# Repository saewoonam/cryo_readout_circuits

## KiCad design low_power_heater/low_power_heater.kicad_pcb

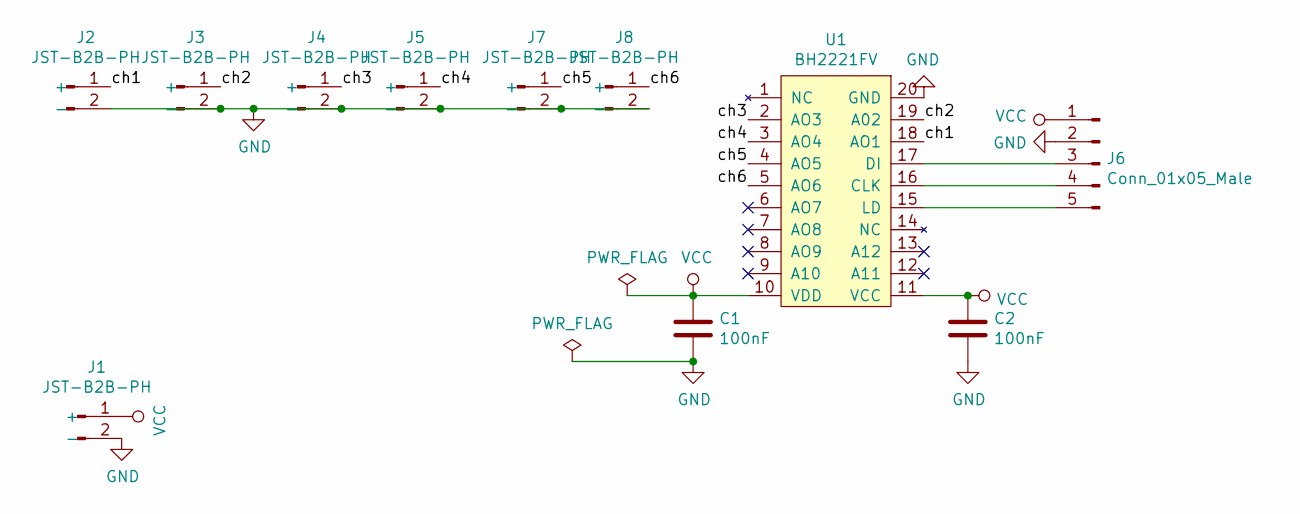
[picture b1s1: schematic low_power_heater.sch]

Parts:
C1, C2: 100nF; C_0603_1608Metric_Pad1.05x0.95mm_HandSolder; MPN CC0603KRX7R9BB104; LCSC C14663
J1, J2, J3, J4, J5, J7, J8: JST-B2B-PH; JST_PH_S2B-PH-SM4-TB_1x02-1MP_P2.00mm_Horizontal; MPN S2B-PH-SM4-TB(LF)(SN); LCSC C295747
J6: Conn_01x05_Male; PinHeader_1x05_P2.54mm_Horizontal; MPN PZ254R-11-05P; LCSC C492413
U1: BH2221FV; SSOP-20_4.4x6.5mm_P0.65mm; MPN BH2221FV-E2; LCSC C2679449

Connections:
/ch1: J2.1 (+), U1.18 (AO1)
/ch2: J3.1 (+), U1.19 (A02)
/ch3: J4.1 (+), U1.2 (AO3)
/ch4: J5.1 (+), U1.3 (AO4)
/ch5: J7.1 (+), U1.4 (AO5)
/ch6: J8.1 (+), U1.5 (AO6)
GND: C1.2, C2.2, J1.2 (-), J2.2 (-), J3.2 (-), J4.2 (-), J5.2 (-), J6.2, J7.2 (-), J8.2 (-), U1.20 (GND)
unnamed: J6.3, U1.17 (DI)
unnamed: J6.4, U1.16 (CLK)
unnamed: J6.5, U1.15 (LD)
VCC: C1.1, C2.1, J1.1 (+), J6.1, U1.10 (VDD), U1.11 (VCC)

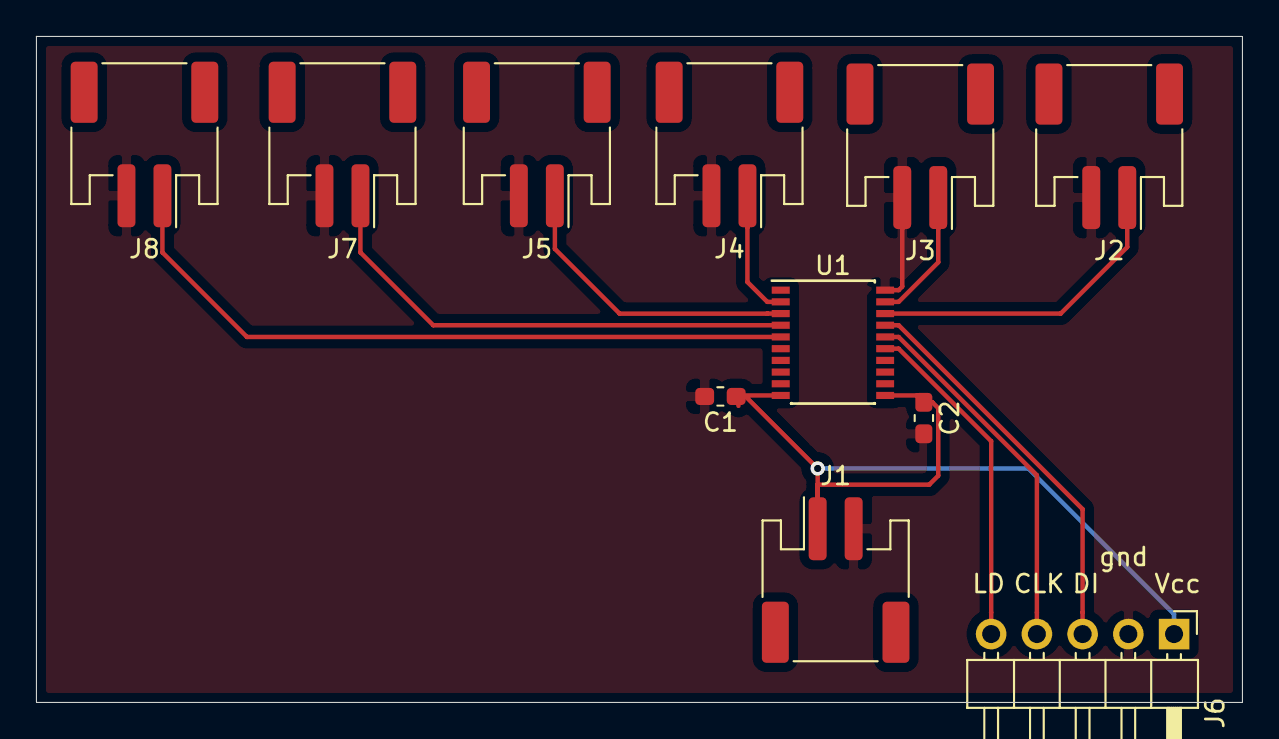
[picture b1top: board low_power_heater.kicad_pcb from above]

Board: 2 copper layers, 67.0 x 37.0 mm, 11 parts (0 on the bottom side), 11 nets.

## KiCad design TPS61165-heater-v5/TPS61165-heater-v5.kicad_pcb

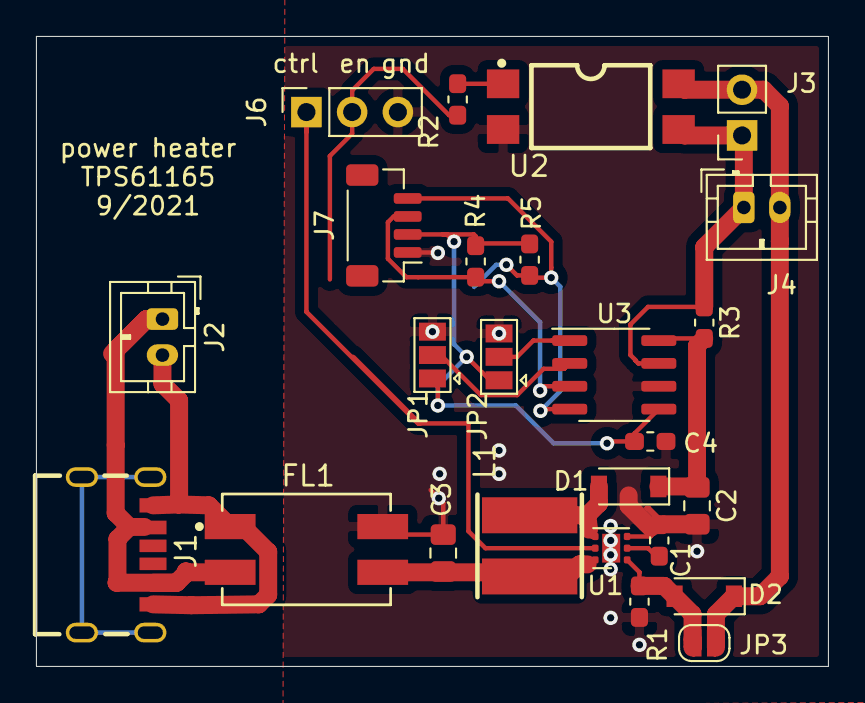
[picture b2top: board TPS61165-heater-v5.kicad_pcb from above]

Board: 2 copper layers, 44.0 x 35.0 mm, 25 parts (0 on the bottom side), 18 nets.

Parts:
C1: 220nF; C_0603_1608Metric_Pad1.05x0.95mm_HandSolder
C2: 1uF_0805_50V; C_0805_2012Metric_Pad1.15x1.40mm_HandSolder
C3: 4.7uF_0805_25V; C_0805_2012Metric_Pad1.15x1.40mm_HandSolder
C4: 100nF; C_0603_1608Metric_Pad1.05x0.95mm_HandSolder
D1: MBR0540; D_SOD-123
D2: BZT52Bxx; D_SOD-123
FL1: EMI_Filter_LL; LL_FILTER-SMD_4P-L9.2-W6.0-TL
J1: USB_C_KoreanHroparts_6P; USB-C-KoreanHroparts
J2, J4: A2001WV-2P; JST_PH_B2B-PH-K_1x02_P2.00mm_Vertical
J3: Conn_01x02_Female; PinSocket_1x02_P2.54mm_Vertical
J6: Conn_01x03_Female; PinSocket_1x03_P2.54mm_Vertical
J7: A1001WV-S-04P; JST_SH_BM04B-SRSS-TB_1x04-1MP_P1.00mm_Vertical
JP1, JP2: Jumper_3_Open; SolderJumper-3_P1.3mm_Open_Pad1.0x1.5mm
JP3: Jumper_2_Open; SolderJumper-2_P1.3mm_Open_RoundedPad1.0x1.5mm
L1: 10uH; IND-SMD_L4.7-W4.7
R1, R3: 1; R_0603_1608Metric_Pad1.05x0.95mm_HandSolder
R2: 390; R_0603_1608Metric_Pad1.05x0.95mm_HandSolder
R4, R5: 4.99K; R_0603_1608Metric_Pad1.05x0.95mm_HandSolder
U1: TPS61165; WSON-6-1EP_2x2mm_P0.65mm_EP1x1.6mm
U2: KAQY212A; SMD-4_L4.6-W6.4-P2.54-LS10.0-BR
U3: INA219AxD; SOIC-8_3.9x4.9mm_P1.27mm

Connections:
+5VD: C3.1, FL1.3, L1.1, U1.6
/scl: J7.4, R5.1, U3.4
/sda: J7.3, R4.1, U3.3
GND: C1.2, C2.2, C3.2, C4.2, FL1.4, J6.3, J7.1, JP1.3, JP2.3, R1.2, U1.3, U1.7, U2.2, U3.6
unnamed: C1.1, U1.2
unnamed: C2.1, D1.1, R3.2, U3.8
unnamed: C4.1, J7.2, JP1.1, JP2.1, R4.2, R5.2, U3.5
unnamed: D1.2, L1.2, U1.4
unnamed: D2.1, J3.2, J4.2, JP3.2, U2.4
unnamed: D2.2, JP3.1, R1.1, U1.1
unnamed: FL1.1, J1.A12, J1.B12, J2.2
unnamed: FL1.2, J1.A9, J1.B9, J2.1
unnamed: J3.1, J4.1, R3.1, U2.3, U3.7
unnamed: J6.1, U1.5
unnamed: J6.2, R2.1
unnamed: JP1.2, U3.2
unnamed: JP2.2, U3.1
unnamed: R2.2, U2.1

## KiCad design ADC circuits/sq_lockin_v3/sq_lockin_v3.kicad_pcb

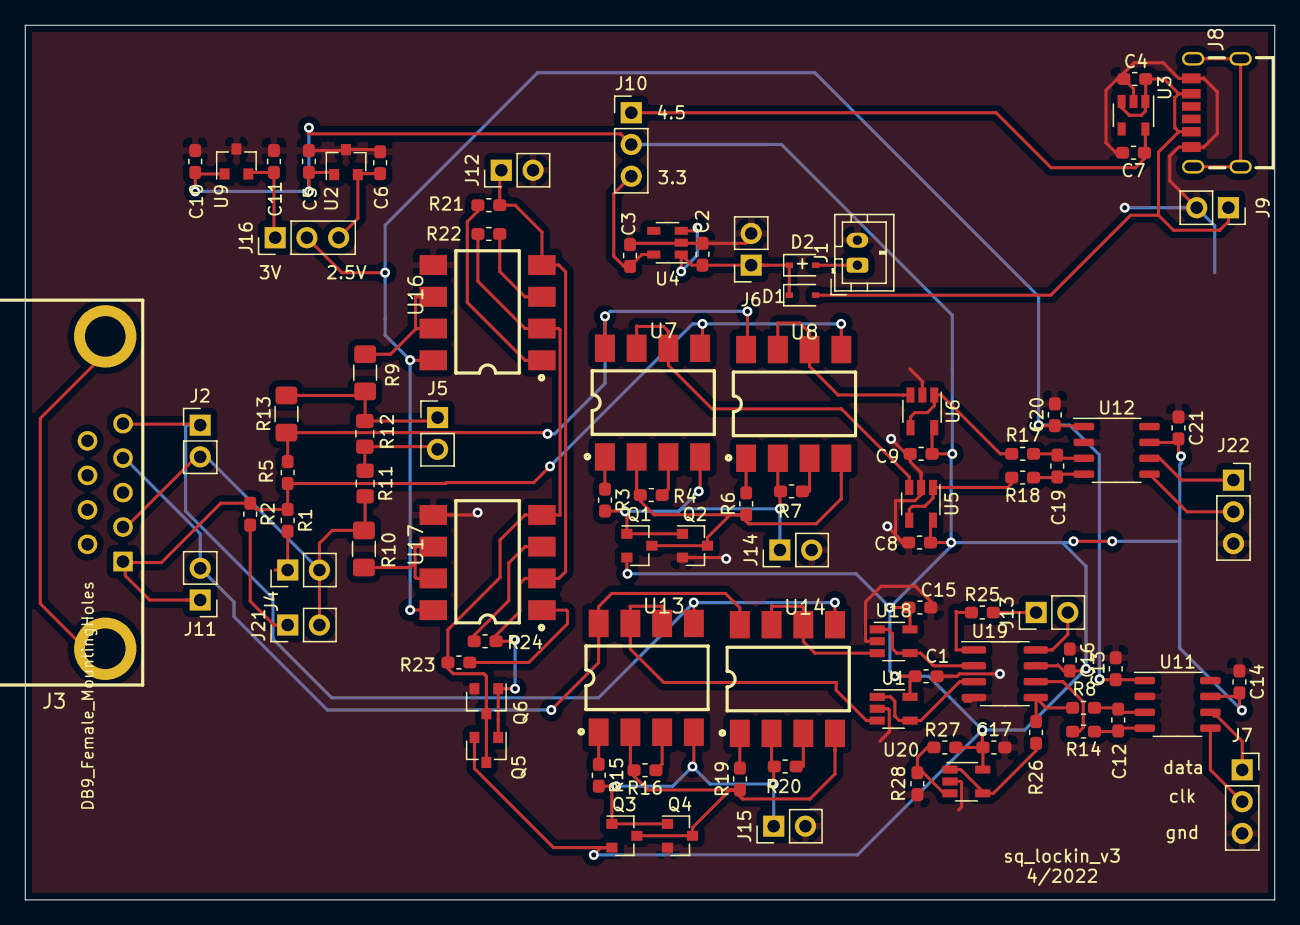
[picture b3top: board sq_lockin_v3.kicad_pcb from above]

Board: 2 copper layers, 100.0 x 70.0 mm, 92 parts (0 on the bottom side), 62 nets.

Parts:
C1, C8, C9, C12, C13, C14, C15, C16, C17, C19, C20, C21: 100nF; C_0603_1608Metric_Pad1.05x0.95mm_HandSolder
C2, C3, C4, C5, C6, C7, C10, C11: 1uF; C_0603_1608Metric_Pad1.05x0.95mm_HandSolder
D1, D2: LBAT54HT1G; D_SOD-323
J1: battery; JST_PH_B2B-PH-K_1x02_P2.00mm_Vertical
J2, J4, J5, J11, J12, J13, J14, J15, J21: Conn_01x02_Male_2.54mm; PinHeader_1x02_P2.54mm_Vertical
J3: DB9_Female_MountingHoles; DSUB-TH_DS1037-09FNAKT74-0CC
J6, J9: receptacle; PinSocket_1x02_P2.54mm_Vertical
J7, J22: Conn_01x03_Female; PinSocket_1x03_P2.54mm_Vertical
J8: USB_C_KoreanHroparts_6P; USB-C-KoreanHroparts
J10, J16: Conn_01x03_Male; PinHeader_1x03_P2.54mm_Vertical
Q1, Q3, Q5: BSS84; SOT-23
Q2, Q4, Q6: 2N7002; SOT-23
R1: 10K 0.1%; R_0603_1608Metric_Pad1.05x0.95mm_HandSolder
R2: 1K 0.1%; R_0603_1608Metric_Pad1.05x0.95mm_HandSolder
R3, R4, R6, R7, R15, R16, R19, R20, R21, R22, R23, R24: 200; R_0603_1608Metric_Pad1.05x0.95mm_HandSolder
R5: 100K_0.1%; R_0603_1608Metric_Pad1.05x0.95mm_HandSolder
R8, R14, R17, R18, R25: 100; R_0603_1608Metric_Pad1.05x0.95mm_HandSolder
R9, R10, R13: 1M_0.1%; R_1206_3216Metric_Pad1.42x1.75mm_HandSolder
R11: 5K_0.1%; R_0805_2012Metric_Pad1.15x1.40mm_HandSolder
R12: 75K_0.1%; R_0805_2012Metric_Pad1.15x1.40mm_HandSolder
R26: 10; R_0603_1608Metric_Pad1.05x0.95mm_HandSolder
R27, R28: 10K; R_0603_1608Metric_Pad1.05x0.95mm_HandSolder
U1, U5, U6, U18, U20: LMP7715; TSOT-23-5
U2: REF3325; SOT-23
U3: LP5907MFX-4.5; SOT-23-5
U4: LP5907MFX-3.3; SOT-23-5
U7, U8, U13, U14, U16, U17: AQW212EHAX; SMD-8_L9.8-W6.4-P2.54-LS10.0-BL
U9: REF3030; SOT-23
U11, U12: HX710C; SOP-8_3.9x4.9mm_P1.27mm
U19: AD623; SOIC-8_3.9x4.9mm_P1.27mm

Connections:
+3V3: C3.1, J10.3, U4.5
+4V: C7.1, J10.1, U3.5
/I+: J3.1, J11.1, R1.1, R2.1, R5.1, U7.5, U8.5
/I-: J2.2, J3.2, J4.2, J21.2, R10.2, R11.2
/Sheet621A3D16/in+: U5.3, U7.6, U7.7
/Sheet621A3D16/in-: U6.3, U8.6, U8.7
/Sheet624B5D4E/ctrl+: J14.1, Q1.1, Q2.1, R3.2, R7.1, U7.4, U8.2
/Sheet624B5D4E/ctrl-: Q1.3, Q2.3, R4.2, R6.1, U7.2, U8.4
/Sheet624B5D4E/in+: R5.2, R13.1, U7.8, U8.8
/Sheet6275CBF8/in+: U1.3, U13.6, U13.7
/Sheet6275CBF8/in-: U14.6, U14.7, U18.3
/Sheet62237673/V+: R18.2, U5.1, U5.4
/Sheet62237673/V-: R17.2, U6.1, U6.4
/V+: J3.4, J11.2, U13.8, U14.8
/V-: J2.1, J3.5, U13.5, U14.5
/sheet624D2E57/V+: R14.2, U19.6
/sheet624D2E57/V-: R8.2, R26.2, U19.5
/sheet624D2E58/ctrl+: J15.1, Q3.1, Q4.1, R15.2, R20.1, U13.4, U14.2
/sheet624D2E58/ctrl-: Q3.3, Q4.3, R16.2, R19.1, U13.2, U14.4
/sheet6256EE2A/ctrl+: J12.1, Q5.1, Q6.1, R21.2, R24.1, U16.4, U17.2
/sheet6256EE2A/ctrl-: Q5.3, Q6.3, R22.2, R23.1, U16.2, U17.4
/sheet6256EE2A/out+: R9.2, U16.6, U16.7
/sheet6256EE2A/out-: R10.1, U17.6, U17.7
/vref: C13.1, C20.1, J16.2, U11.1, U12.1, U16.8, U17.8
/vref1: C6.1, J16.3, U2.2
/vref2: C11.1, J16.1, U9.2
GND: C1.2, C2.2, C3.2, C4.2, C5.2, C6.2, C7.2, C8.2, C9.2, C10.2, C11.2, C13.2, C14.1, C15.2, C16.1, C17.2, C20.2, C21.1, J1.2, J6.2, J7.3, J8.A12, J8.B12, J9.2, J12.2, J14.2, J15.2, J22.3, Q2.2, Q4.2, Q6.2, R28.2, U1.2, U2.3, U3.2, U4.2, U5.2, U6.2, U9.3, U11.2, U12.2, U16.5, U17.5, U18.2, U19.4, U20.2
unnamed: C2.1, D1.1, D2.1, J6.1, U4.1, U4.3
unnamed: C4.1, D1.2, J8.A9, J8.B9, J9.1, U3.1, U3.3
unnamed: C12.1, R14.1, U11.4
unnamed: C12.2, R8.1, U11.3
unnamed: C19.1, R18.1, U12.4
unnamed: C19.2, R17.1, U12.3
unnamed: D2.2, J1.1
unnamed: J4.1, R1.2
unnamed: J5.1, R9.1, R12.1, R13.2
unnamed: J5.2, R11.1, R12.2
unnamed: J7.1, U11.6
unnamed: J7.2, U11.5
unnamed: J13.1, R25.2
unnamed: J13.2, U19.8
unnamed: J21.1, R2.2
unnamed: J22.1, U12.6
unnamed: J22.2, U12.5
unnamed: R3.1, U7.1
unnamed: R4.1, U7.3
unnamed: R6.2, U8.1
unnamed: R7.2, U8.3
unnamed: R15.1, U13.1
unnamed: R16.1, U13.3
unnamed: R19.2, U14.1
unnamed: R20.2, U14.3
unnamed: R21.1, U16.1
unnamed: R22.1, U16.3
unnamed: R23.2, U17.1
unnamed: R24.2, U17.3
unnamed: R25.1, U19.1
unnamed: R26.1, U20.1, U20.4
unnamed: R27.2, R28.1, U20.3
unnamed: U1.1, U1.4, U19.3
unnamed: U18.1, U18.4, U19.2
VCC: C1.1, C5.1, C8.1, C9.1, C10.1, C14.2, C15.1, C16.2, C17.1, C21.2, J10.2, Q1.2, Q3.2, Q5.2, R27.1, U1.5, U2.1, U5.5, U6.5, U9.1, U11.7, U12.7, U18.5, U19.7, U20.5

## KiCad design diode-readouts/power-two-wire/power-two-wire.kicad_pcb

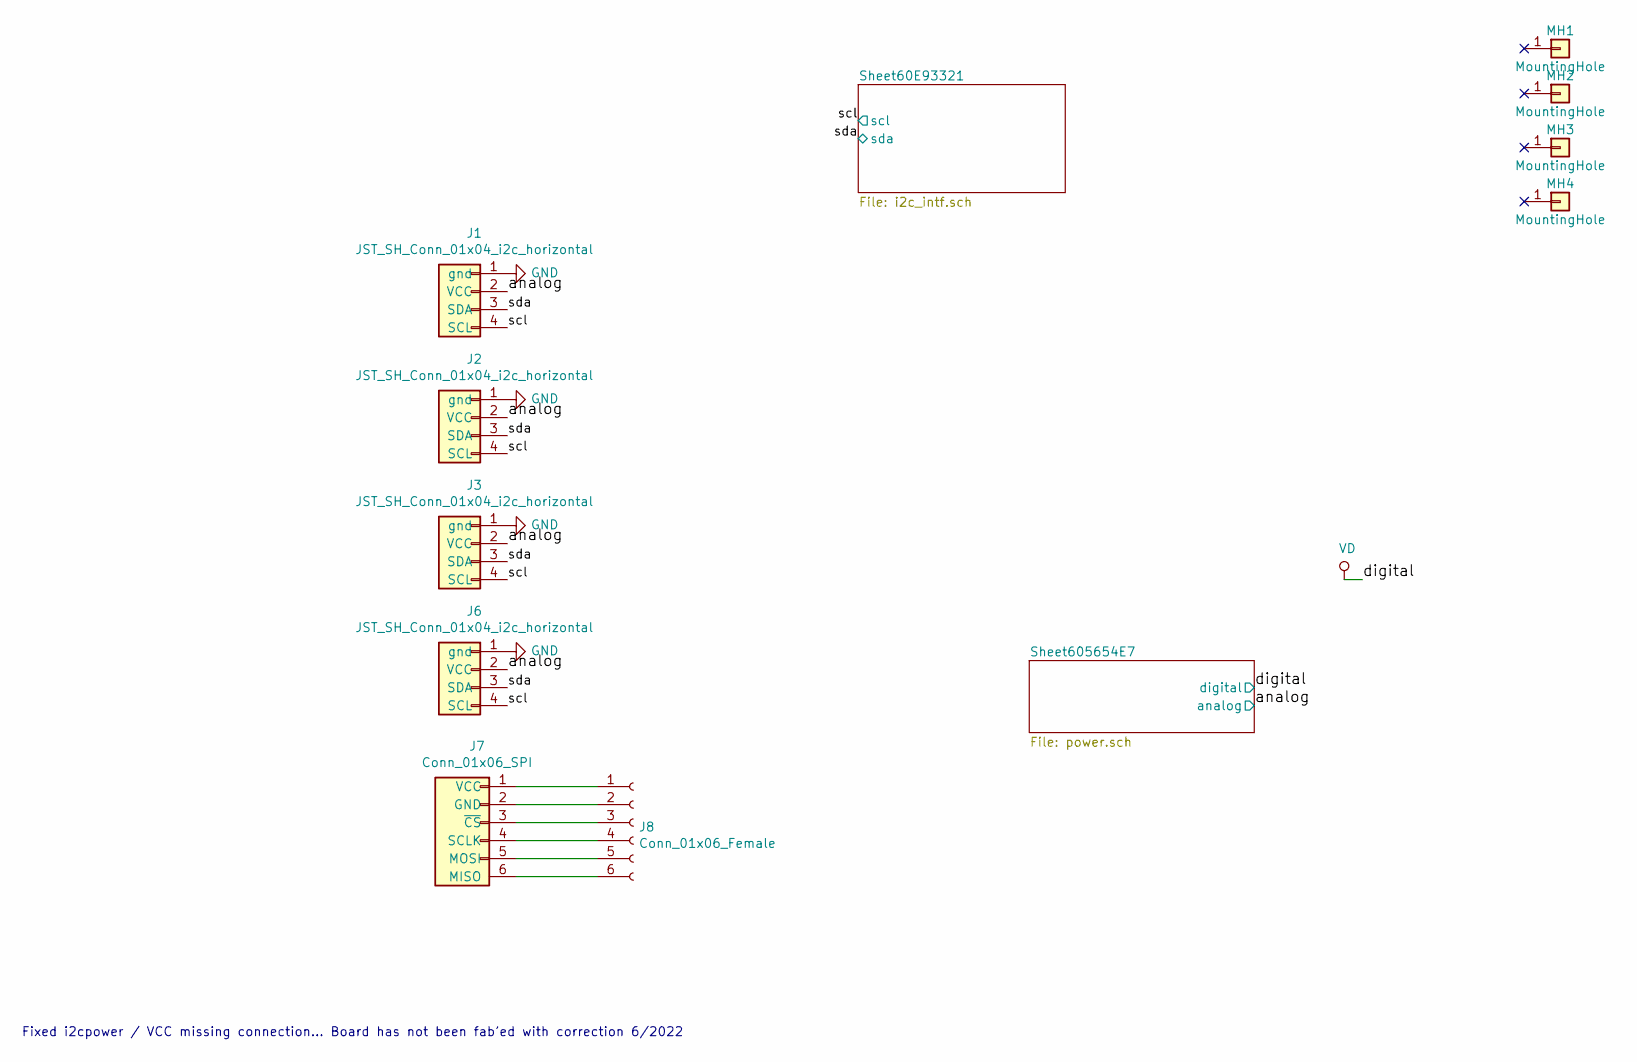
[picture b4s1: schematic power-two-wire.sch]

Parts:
J1, J2, J3, J6: JST_SH_Conn_01x04_i2c_horizontal; JST_SH_SM04B-SRSS-TB_1x04-1MP_P1.00mm_Horizontal; MPN A1001WR-S; LCSC C371571
J7: Conn_01x06_SPI; JST_SH_SM06B-SRSS-TB_1x06-1MP_P1.00mm_Horizontal; MPN A1001WR-S-06PD01; LCSC C371573
J8: Conn_01x06_Female; PinSocket_1x06_P2.54mm_Vertical
MH1, MH2, MH3, MH4: MountingHole; MountingHole_3.5mm_Pad

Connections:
/analog: J1.2 (VCC), J2.2 (VCC), J3.2 (VCC), J6.2 (VCC); also elsewhere on the board
/scl: J1.4 (SCL), J2.4 (SCL), J3.4 (SCL), J6.4 (SCL); also elsewhere on the board
/sda: J1.3 (SDA), J2.3 (SDA), J3.3 (SDA), J6.3 (SDA); also elsewhere on the board
GND: J1.1 (gnd), J2.1 (gnd), J3.1 (gnd), J6.1 (gnd); also elsewhere on the board
unnamed: J7.1 (VCC), J8.1
unnamed: J7.2 (GND), J8.2
unnamed: J7.3 (~CS), J8.3
unnamed: J7.4 (SCLK), J8.4
unnamed: J7.5 (MOSI), J8.5
unnamed: J7.6 (MISO), J8.6

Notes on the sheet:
Fixed i2cpower / VCC missing connection… Board has not been fab’ed with correction 6/2022

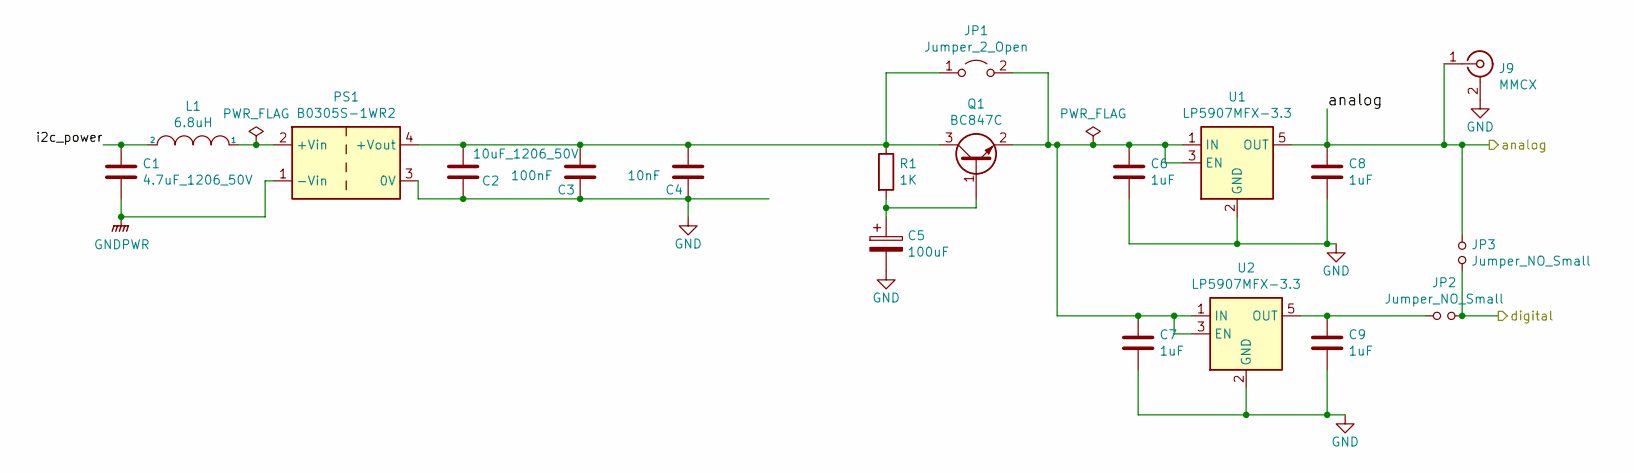
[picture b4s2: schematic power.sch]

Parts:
C1: 4.7uF_1206_50V; C_1206_3216Metric_Pad1.42x1.75mm_HandSolder; MPN 1206B475K500NT; LCSC C29823
C2: 10uF_1206_50V; C_1206_3216Metric_Pad1.42x1.75mm_HandSolder; MPN CL31A106KBHNNNE; LCSC C13585
C3: 100nF; C_0603_1608Metric_Pad1.05x0.95mm_HandSolder; MPN CC0603KRX7R9BB104; LCSC C14663
C4: 10nF; C_0603_1608Metric_Pad1.05x0.95mm_HandSolder; MPN 0603B103K500NT; LCSC C57112
C5: 100uF; CP_EIA-3528-12_Kemet-T; MPN GRM32ER61A107ME20L; LCSC C84455
C6, C7, C8, C9: 1uF; C_0603_1608Metric_Pad1.05x0.95mm_HandSolder; MPN CL10A105KB8NNNC; LCSC C15849
J9: MMCX; MMCX_JLC; MPN KH-MMCX-Z; LCSC C530664
JP1: Jumper_2_Open; SolderJumper-2_P1.3mm_Open_RoundedPad1.0x1.5mm
JP2, JP3: Jumper_NO_Small; SolderJumper-2_P1.3mm_Open_Pad1.0x1.5mm
L1: 6.8uH; L_1210_3225Metric_Pad1.42x2.65mm_HandSolder; MPN NLCV32T-6R8M-PFR; LCSC C87559
PS1: B0305S-1WR2; Converter_DCDC_muRata_CRE1xxxxxx3C_THT; MPN B0305S-1WR2; LCSC C80854
Q1: BC847C; SOT-23; MPN BC847C,215; LCSC C8664
R1: 1K; R_0603_1608Metric_Pad1.05x0.95mm_HandSolder; MPN 0603WAF1001T5E; LCSC C21190
U1, U2: LP5907MFX-3.3; SOT-23-5; MPN LP5907MFX-3.3/NOPB; LCSC C80670

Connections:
/analog: C8.1, J9.1 (In), JP3.1, U1.5 (OUT); also elsewhere on the board
GND: C2.2, C3.1, C4.1, C5.2, C6.2, C7.2, C8.2, C9.2, J9.2 (Ext), PS1.3 (0V), U1.2 (GND), U2.2 (GND); also elsewhere on the board
GNDPWR: C1.2, PS1.1 (-Vin); also elsewhere on the board
unnamed: C2.1, C3.2, C4.2, JP1.1 (A), PS1.4 (+Vout), Q1.3 (C), R1.1
unnamed: C5.1, Q1.1 (B), R1.2
unnamed: C6.1, C7.1, JP1.2 (B), Q1.2 (E), U1.1 (IN), U1.3 (EN), U2.1 (IN), U2.3 (EN)
unnamed: C9.1, JP2.2, U2.5 (OUT)
unnamed: L1.1, PS1.2 (+Vin)
VCC: C1.1, L1.2; also elsewhere on the board
VD: JP2.1, JP3.2; also elsewhere on the board

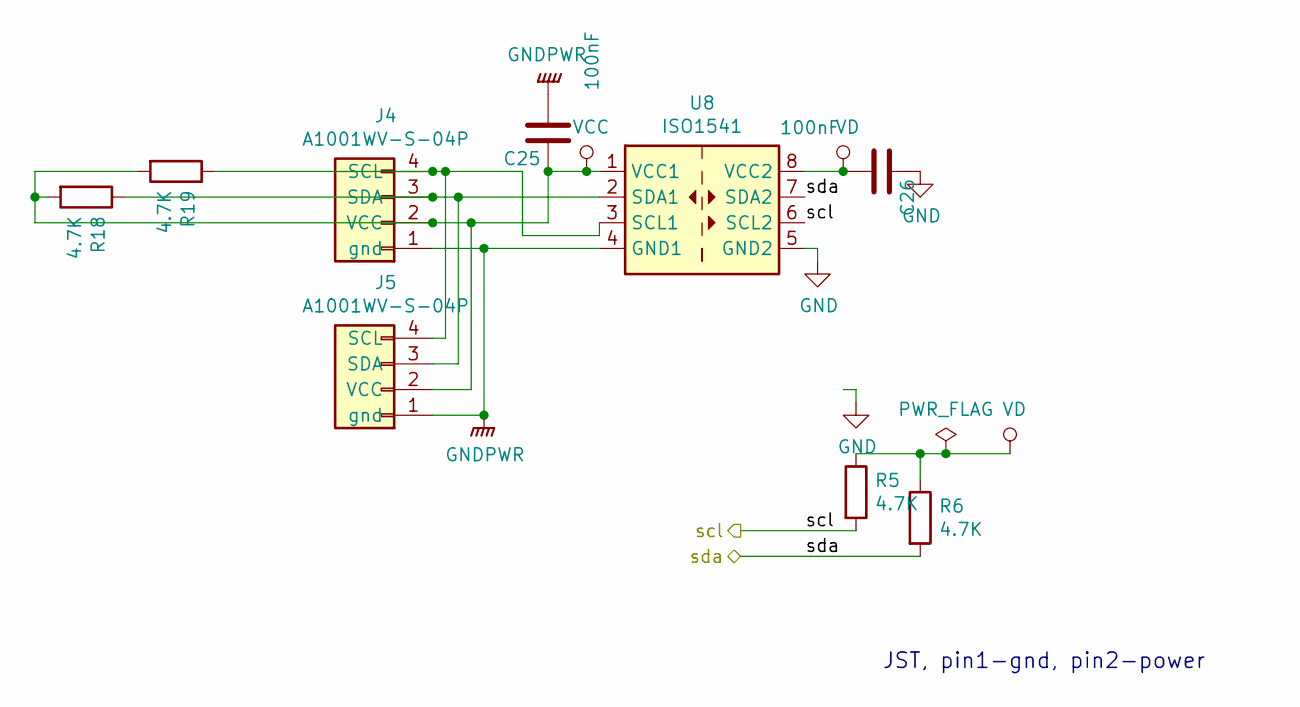
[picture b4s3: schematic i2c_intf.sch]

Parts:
C25, C26: 100nF; C_0603_1608Metric_Pad1.05x0.95mm_HandSolder; MPN CC0603KRX7R9BB104; LCSC C14663
J4, J5: A1001WV-S-04P; JST_SH_SM04B-SRSS-TB_1x04-1MP_P1.00mm_Horizontal; MPN A1001WR-S-04PD01; LCSC C371571
R5, R6, R18, R19: 4.7K; R_0603_1608Metric_Pad1.05x0.95mm_HandSolder; MPN RC0603FR-074K7L; LCSC C23162
U8: ISO1541; SOIC-8_3.9x4.9mm_P1.27mm; MPN ISO1541DR; LCSC C143028

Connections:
/scl: R5.2, U8.6 (SCL2); also elsewhere on the board
/sda: R6.2, U8.7 (SDA2); also elsewhere on the board
GND: C26.1, U8.5 (GND2); also elsewhere on the board
GNDPWR: C25.2, J4.1 (gnd), J5.1 (gnd), U8.4 (GND1); also elsewhere on the board
unnamed: J4.3 (SDA), J5.3 (SDA), R18.1, U8.2 (SDA1)
unnamed: J4.4 (SCL), J5.4 (SCL), R19.1, U8.3 (SCL1)
VCC: C25.1, J4.2 (VCC), J5.2 (VCC), R18.2, R19.2, U8.1 (VCC1); also elsewhere on the board
VD: C26.2, R5.1, R6.1, U8.8 (VCC2); also elsewhere on the board

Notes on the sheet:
JST, pin1-gnd, pin2-power

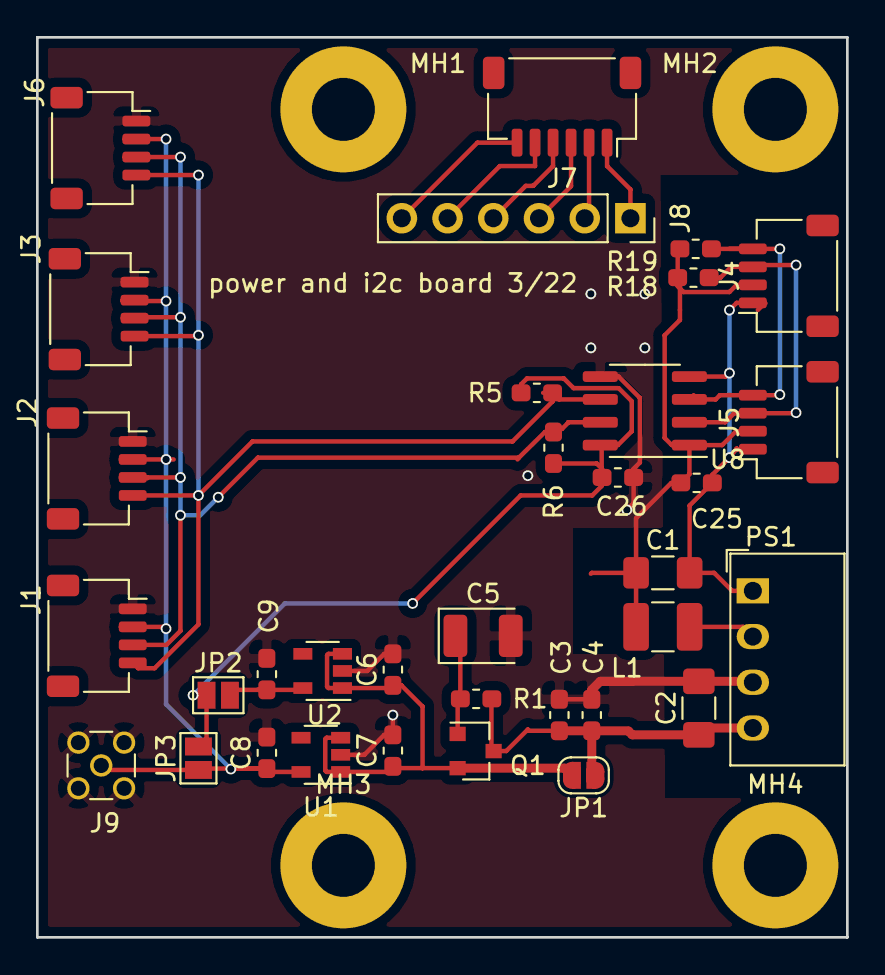
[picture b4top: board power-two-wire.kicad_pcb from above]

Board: 2 copper layers, 45.0 x 50.0 mm, 38 parts (0 on the bottom side), 20 nets.

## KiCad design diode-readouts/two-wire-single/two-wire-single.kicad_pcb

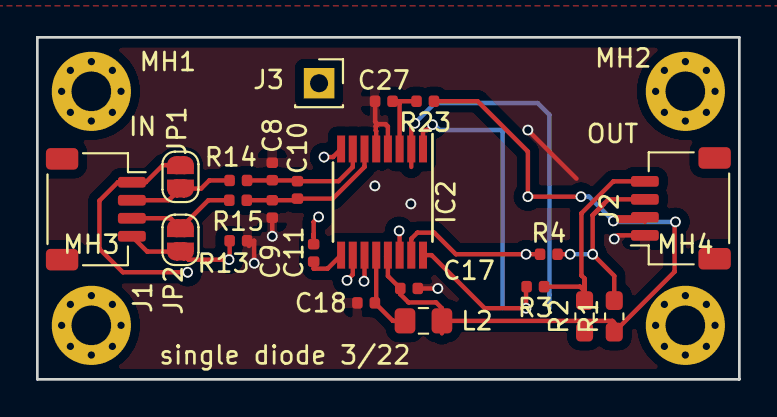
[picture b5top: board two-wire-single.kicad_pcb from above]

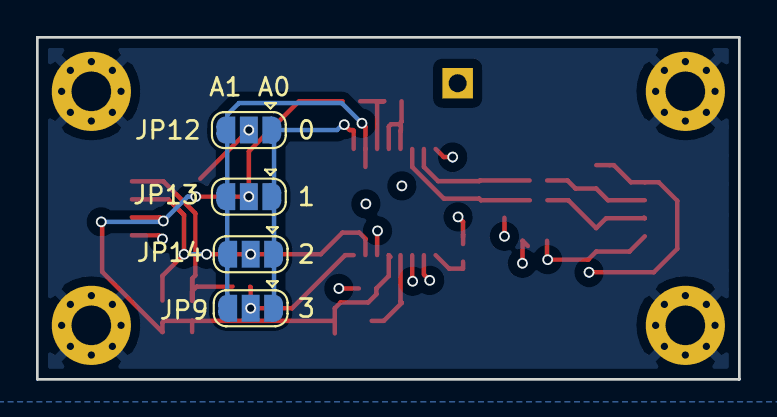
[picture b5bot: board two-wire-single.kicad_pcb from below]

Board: 4 copper layers, 39.0 x 19.0 mm, 30 parts (4 on the bottom side), 20 nets.

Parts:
C8, C9, C11, C17, C18, C27: 100nF; C_0402_1005Metric
C10: 1uF; C_0402_1005Metric
IC2: ADS112C04IPWR; TSSOP-16_4.4x5mm_P0.65mm
J1: Conn_01x04; JST_SH_SM04B-SRSS-TB_1x04-1MP_P1.00mm_Horizontal
J2: JST_SH_Conn_01x04_i2c_horizontal; JST_SH_SM04B-SRSS-TB_1x04-1MP_P1.00mm_Horizontal
J3: Conn_01x01_Female; PinSocket_1x01_P2.54mm_Vertical
JP1, JP2: Jumper_NO_Small; SolderJumper-2_P1.3mm_Open_RoundedPad1.0x1.5mm
JP9, JP12, JP13, JP14: Jumper_3_Open; SolderJumper-3_P1.3mm_Open_RoundedPad1.0x1.5mm
L2: MMZ2012Y202B; L_0805_2012Metric_Pad1.15x1.40mm_HandSolder
MH1, MH2, MH3, MH4: MountingHole; MountingHole_2.2mm_M2_Pad_Via
R1, R2: 10K; R_0603_1608Metric_Pad1.05x0.95mm_HandSolder
R3, R4: 47; R_0402_1005Metric
R13: 10K 0.1%; R_0402_1005Metric
R14, R15: 100K; R_0402_1005Metric
R23: 1K; R_0402_1005Metric

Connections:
/Channel1/A0: IC2.1, JP9.1, JP12.1, JP13.1, JP14.1
/Channel1/A1: IC2.2, JP9.3, JP12.3, JP13.3, JP14.3
/Channel1/I+: IC2.11, J1.1, JP1.1
/Channel1/I-: IC2.10, J1.4, JP2.2, R13.1
/Channel1/SCL: IC2.16, JP9.2, R3.2
/Channel1/SDA: IC2.15, JP14.2, R4.1
/Channel1/V+: J1.2, JP1.2, R14.2
/Channel1/V-: J1.3, JP2.1, R15.2
/Channel1/Vpower: C18.2, IC2.12, L2.2
/Channel1/~DRDY: IC2.14, J3.1
/scl-rx: J2.4, R2.2, R3.1
/sda-tx: J2.3, R1.2, R4.2
GND: C8.1, C9.2, C17.2, C18.1, C27.1, IC2.4, IC2.5, J2.1, JP12.2, R13.2
GNDPWR: MH1.1, MH2.1, MH3.1, MH4.1
unnamed: C8.2, C10.1, IC2.7, R14.1
unnamed: C9.1, C10.2, IC2.6, R15.1
unnamed: C11.1, IC2.9
unnamed: C11.2, IC2.8
unnamed: C27.2, IC2.3, R23.2
VD: C17.1, IC2.13, J2.2, JP13.2, L2.1, R1.1, R2.1, R23.1

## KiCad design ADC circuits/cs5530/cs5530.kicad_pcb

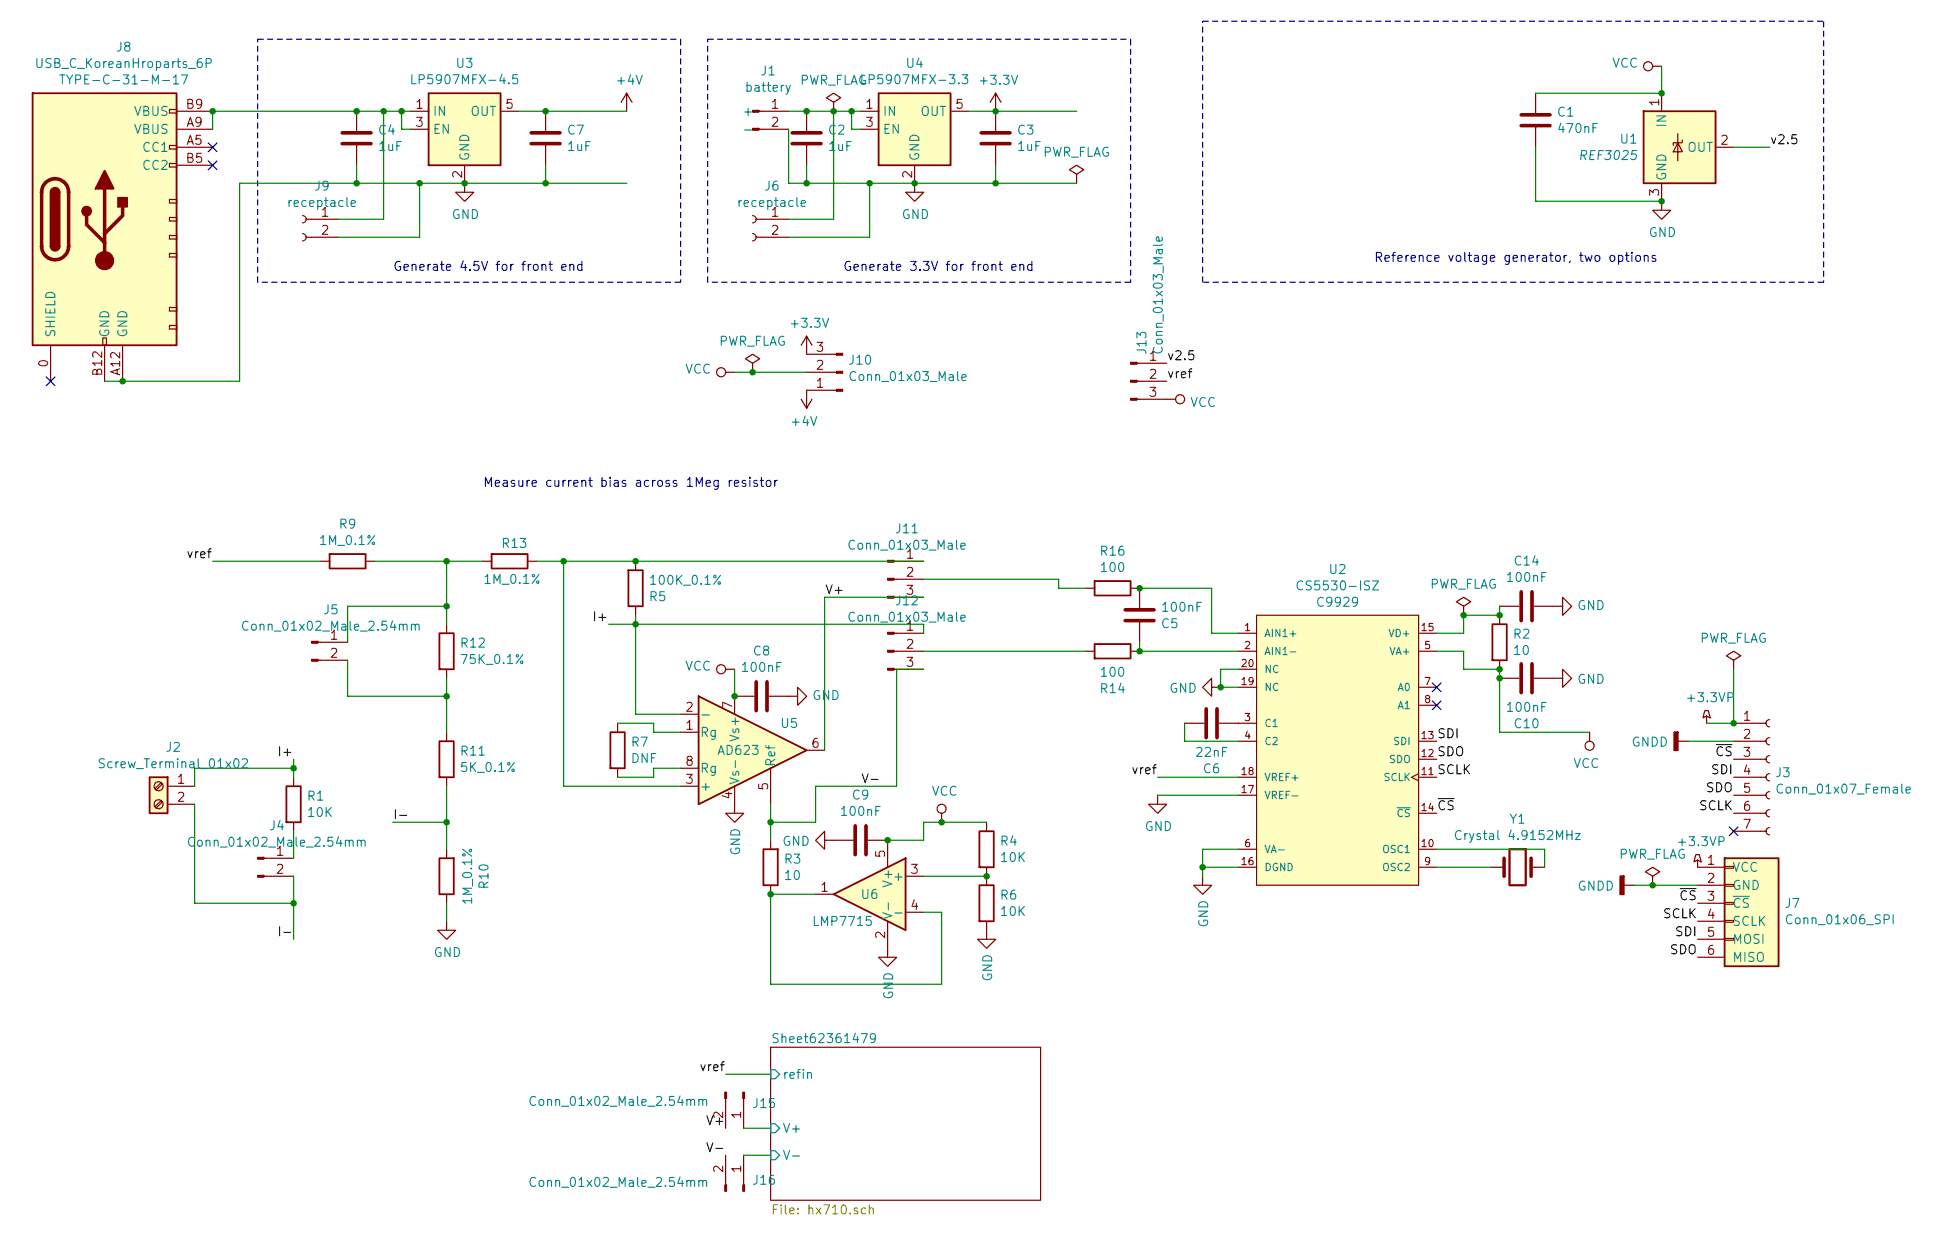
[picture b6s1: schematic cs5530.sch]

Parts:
C1: 470nF; C_0603_1608Metric_Pad1.05x0.95mm_HandSolder; MPN CL10B474KA8NNNC; LCSC C1623
C2, C3, C4, C7: 1uF; C_0603_1608Metric_Pad1.05x0.95mm_HandSolder; MPN CL10A105KB8NNNC; LCSC C15849
C5, C8, C9, C10, C14: 100nF; C_0603_1608Metric_Pad1.05x0.95mm_HandSolder; MPN CC0603KRX7R9BB104; LCSC C14663
C6: 22nF; C_0603_1608Metric_Pad1.05x0.95mm_HandSolder; MPN 0603B223K500; LCSC C123507
J1: battery; JST_PH_B2B-PH-K_1x02_P2.00mm_Vertical; MPN B2B-PH-K-S(LF)(SN); LCSC C131337
J2: Screw_Terminal_01x02; TerminalBlock_Phoenix_MKDS-1,5-2-5.08_1x02_P5.08mm_Horizont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; LCSC C395868
J3: Conn_01x07_Female; PinSocket_1x07_P2.54mm_Vertical; MPN B-2200S07P-A120; LCSC C124418
J4, J5, J15, J16: Conn_01x02_Male_2.54mm; PinHeader_1x02_P2.54mm_Vertical; MPN PZ254V-11-02P; LCSC C492401
J6, J9: receptacle; PinSocket_1x02_P2.54mm_Vertical; MPN HDR-TH_2P-P2.54-V-M; LCSC C49661
J7: Conn_01x06_SPI; JST_B6B-ZR(LF)(SN); MPN B6B-ZR(LF)(SN); LCSC C157984
J8: USB_C_KoreanHroparts_6P; USB-C-KoreanHroparts; MPN TYPE-C-31-M-17; LCSC C283540
J10, J11, J12, J13: Conn_01x03_Male; PinHeader_1x03_P2.54mm_Vertical; LCSC C49257
R1, R4, R6: 10K; R_0603_1608Metric_Pad1.05x0.95mm_HandSolder; MPN 0603WAF1002T5E; LCSC C25804
R2, R3: 10; R_0603_1608Metric_Pad1.05x0.95mm_HandSolder; MPN 0603WAF100JT5E; LCSC C22859
R5: 100K_0.1%; R_0603_1608Metric_Pad1.05x0.95mm_HandSolder; MPN RT0603BRD07100KL; LCSC C122538
R7: DNF; R_0603_1608Metric_Pad1.05x0.95mm_HandSolder
R9, R10, R13: 1M_0.1%; R_1206_3216Metric_Pad1.42x1.75mm_HandSolder; MPN TC0625B1004T5E; LCSC C130127
R11: 5K_0.1%; R_0805_2012Metric_Pad1.15x1.40mm_HandSolder; MPN TC0525B5001T5E; LCSC C78980
R12: 75K_0.1%; R_0805_2012Metric_Pad1.15x1.40mm_HandSolder; MPN TC0525B7502T5E; LCSC C111588
R14, R16: 100; R_0603_1608Metric_Pad1.05x0.95mm_HandSolder; MPN 0603WAF1000T5E; LCSC C22775
U1: REF3025; SOT-23; MPN REF3025AIDBZR; LCSC C11334
U2: CS5530-ISZ; SSOP-20_5.3x7.2mm_P0.65mm; LCSC C9929
U3: LP5907MFX-4.5; SOT-23-5; MPN LP5907MFX-4.5/NOPB; LCSC C529554
U4: LP5907MFX-3.3; SOT-23-5; MPN LP5907MFX-3.3/NOPB; LCSC C80670
U5: AD623; SOIC-8_3.9x4.9mm_P1.27mm; LCSC C9676
U6: LMP7715; TSOT-23-5; MPN LMP7715MF/NOPB; LCSC C129985
Y1: Crystal 4.9152MHz; Crystal_X49SM49152MSD2SC; MPN X49SM49152MSD2SC-1; LCSC C21921

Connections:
+3.3VP: J3.1, J7.1 (VCC)
+3V3: C3.1, J10.3, U4.5 (OUT)
+4V: C7.1, J10.1, U3.5 (OUT)
/I+: J2.1, J12.1, R1.1, R5.1, U5.2 (-)
/I-: J2.2, J4.2, R10.2, R11.2
/SCLK: J3.6, J7.4 (SCLK), U2.11 (SCLK)
/SDI: J3.4, J7.5 (MOSI), U2.13 (SDI)
/SDO: J3.5, J7.6 (MISO), U2.12 (SDO)
/Sheet62361479/V+: J15.1; also elsewhere on the board
/Sheet62361479/V-: J16.1; also elsewhere on the board
/V+: J11.3, J15.2, U5.6
/V-: J12.3, J16.2, R3.2, U5.5 (Ref)
/v2.5: J13.1, U1.2 (OUT)
/vref: J13.2, R9.2, U2.18 (VREF+); also elsewhere on the board
/~CS: J3.3, J7.3 (~CS), U2.14 (~CS~)
GND: C1.2, C2.2, C3.2, C4.2, C7.2, C8.1, C9.2, C10.1, C14.1, J1.2 (-), J6.2, J8.A12 (GND), J8.B12 (GND), J9.2, R6.2, R10.1, U1.3 (GND), U2.6 (VA-), U2.16 (DGND), U2.17 (VREF-), U2.19 (NC), U2.20 (NC), U3.2 (GND), U4.2 (GND), U5.4 (Vs-), U6.2 (V-); also elsewhere on the board
GNDD: J3.2, J7.2 (GND)
unnamed: C2.1, J1.1 (+), J6.1, U4.1 (IN), U4.3 (EN)
unnamed: C4.1, J8.A9 (VBUS), J8.B9 (VBUS), J9.1, U3.1 (IN), U3.3 (EN)
unnamed: C5.1, R16.1, U2.1 (AIN1+)
unnamed: C5.2, R14.1, U2.2 (AIN1-)
unnamed: C6.1, U2.3 (C1)
unnamed: C6.2, U2.4 (C2)
unnamed: C14.2, R2.1, U2.15 (VD+)
unnamed: J4.1, R1.2
unnamed: J5.1, R9.1, R12.1, R13.2
unnamed: J5.2, R11.1, R12.2
unnamed: J11.1, R5.2, R13.1, U5.3 (+)
unnamed: J11.2, R16.2
unnamed: J12.2, R14.2
unnamed: R3.1, U6.1, U6.4 (-)
unnamed: R4.2, R6.1, U6.3 (+)
unnamed: R7.1, U5.1 (Rg)
unnamed: R7.2, U5.8 (Rg)
unnamed: U2.9 (OSC2), Y1.2
unnamed: U2.10 (OSC1), Y1.1
VCC: C1.1, C8.2, C9.1, C10.2, J10.2, J13.3, R2.2, R4.1, U1.1 (IN), U2.5 (VA+), U5.7 (Vs+), U6.5 (V+); also elsewhere on the board

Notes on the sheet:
Generate 3.3V for front end
Reference voltage generator, two options
Measure current bias across 1Meg resistor
Generate 4.5V for front end

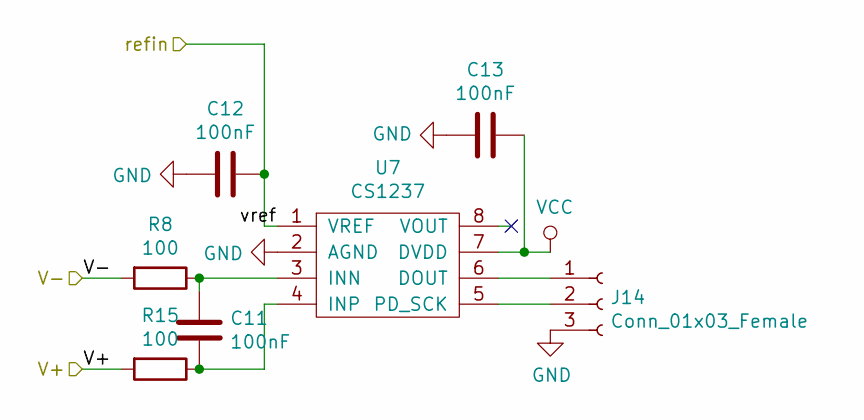
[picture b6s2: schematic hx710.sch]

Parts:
C11, C12, C13: 100nF; C_0603_1608Metric_Pad1.05x0.95mm_HandSolder; MPN CC0603KRX7R9BB104; LCSC C14663
J14: Conn_01x03_Female; PinSocket_1x03_P2.54mm_Vertical; MPN B-2200S03P-A120; LCSC C146690
R8, R15: 100; R_0603_1608Metric_Pad1.05x0.95mm_HandSolder; MPN 0603WAF1000T5E; LCSC C22775
U7: CS1237; SOP-8_3.9x4.9mm_P1.27mm; MPN CS1237-SO; LCSC C77801

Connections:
/Sheet62361479/V+: R15.2; also elsewhere on the board
/Sheet62361479/V-: R8.2; also elsewhere on the board
/vref: C12.1, U7.1 (VREF); also elsewhere on the board
GND: C12.2, C13.1, J14.3, U7.2 (AGND); also elsewhere on the board
unnamed: C11.1, R15.1, U7.4 (INP)
unnamed: C11.2, R8.1, U7.3 (INN)
unnamed: J14.1, U7.6 (DOUT)
unnamed: J14.2, U7.5 (PD_SCK)
VCC: C13.2, U7.7 (DVDD); also elsewhere on the board

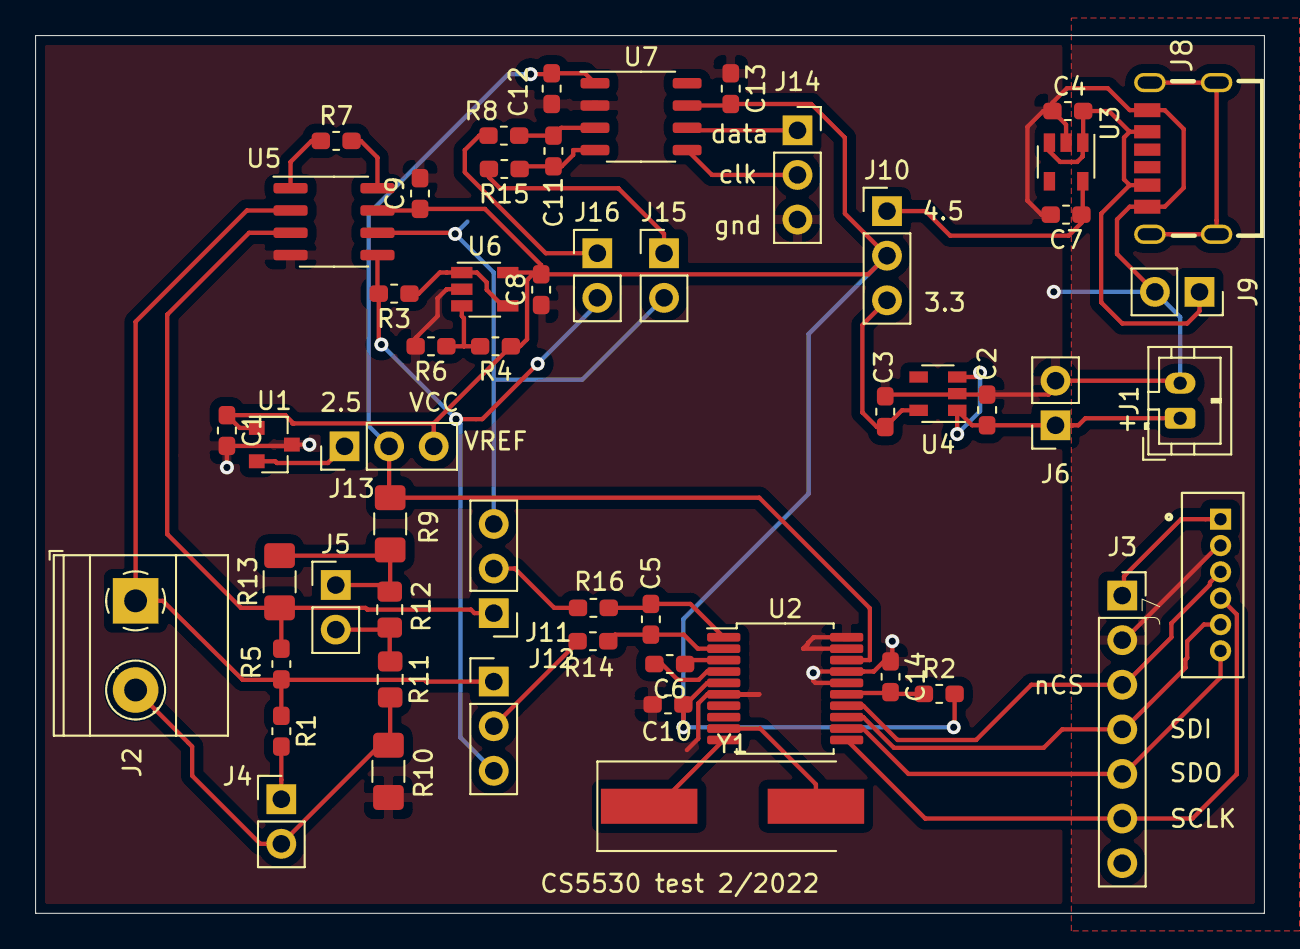
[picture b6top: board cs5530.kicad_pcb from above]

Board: 2 copper layers, 70.0 x 50.0 mm, 54 parts (0 on the bottom side), 41 nets.
